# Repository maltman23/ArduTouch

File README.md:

# ArduTouch

ArduTouch is an Arduino-compatible music synthesizer kit.  
Build it, and it works!  
Way low cost (currently $30.)  
It comes with a pre-programmed music synthesizer that makes way cool sounds and music and noise.

An ArduTouch library is available for programming in more super nice synthesizer features, and for making your own synthesizers.
The library comes with examples (with more to come) that serve as a nice tutorial on how to create your own ArduTouch synthesizers (which are Arduino sketches).

ArduTouch is really just an Arduino Uno clone with a small amplifier & speaker, with a PCB touch keyboard, a couple of extra buttons, and a couple of pots (for playing music and controlling the sounds).  The ArduTouch Arduino Library is where the real magic comes from!

For those who want to learn more, the documentation teaches the basics of Digital Signal Processing for audio generation (more documentation coming soon).

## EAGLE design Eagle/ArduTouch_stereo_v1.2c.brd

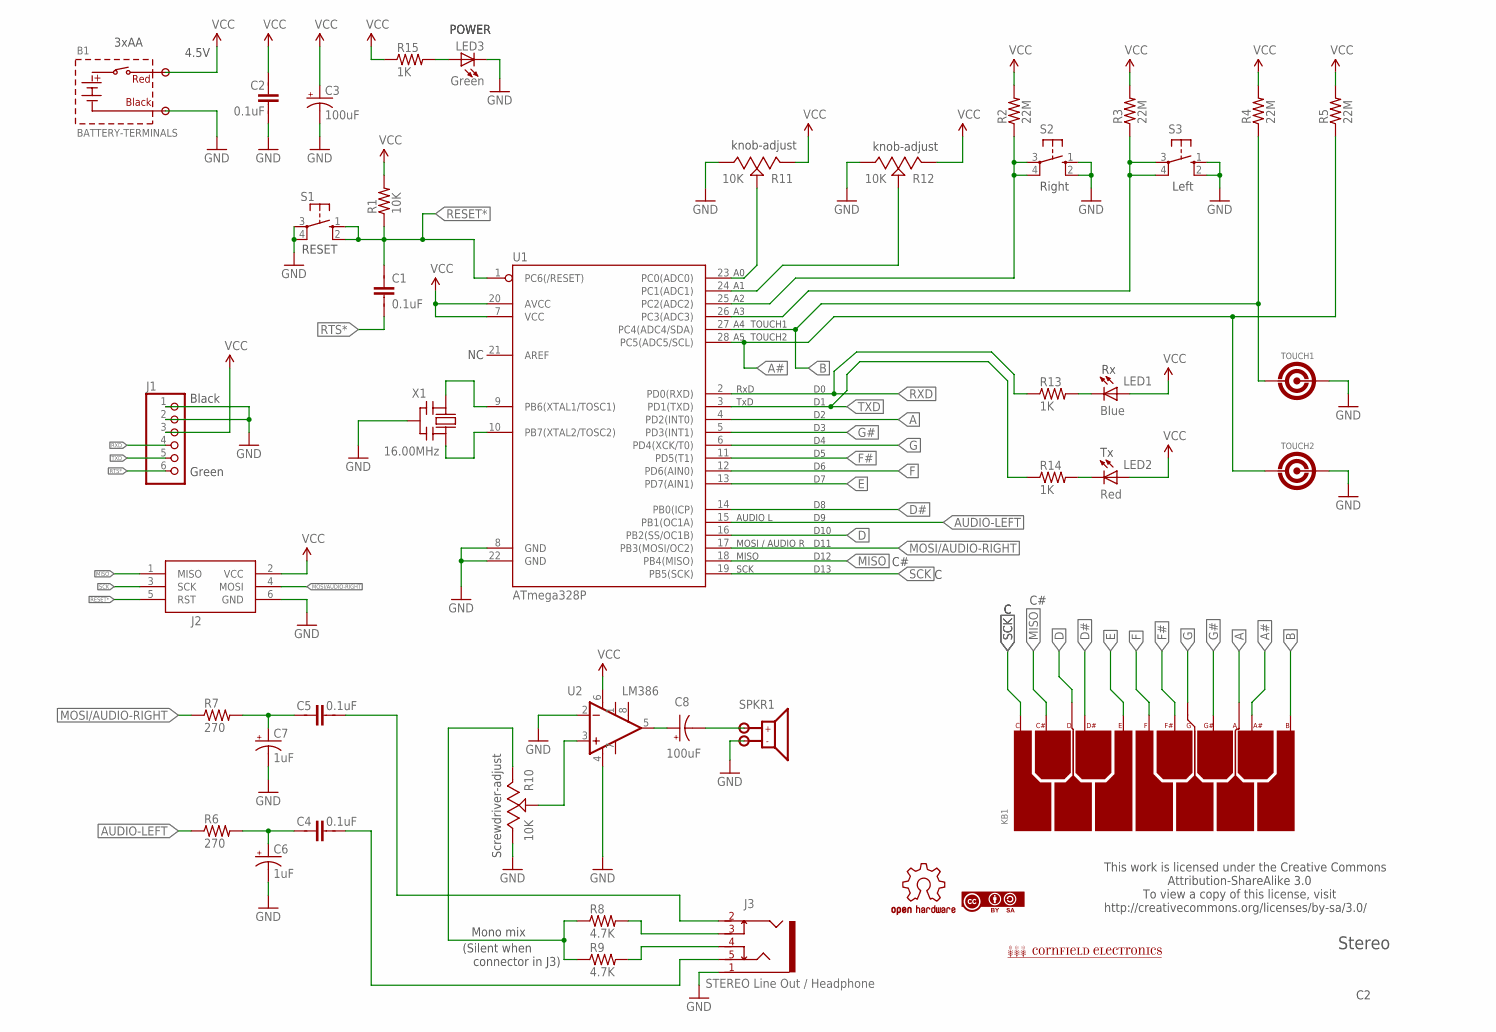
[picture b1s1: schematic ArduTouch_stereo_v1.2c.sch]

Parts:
B1: BATTERY-TERMINALS
C1, C2, C4, C5: 0.1uF; CAP-PTH-SMALL
C3, C8: 100uF; CPOL-RADIAL-10UF-25V
C6, C7: 1uF; CPOL-RADIAL-10UF-25V
J1: PINHD-1X6LOCK; 1X06-BIGLOCK
J2: ISP; AVRISP
J3: STEREO-AUDIO-3.5MM-SWITCHED
KB1: PCB-KEYBOARD4
LED1: Blue; LED5MM
LED2: Red; LED5MM
LED3: Green; LED5MM
R1: 10K; AXIAL-0.4
R2, R3, R4, R5: 22M; AXIAL-0.4
R6, R7: 270; AXIAL-0.4
R8, R9: 4.7K; AXIAL-0.4
R10: 10K; TRIMPOT-3319P-1
R11, R12: 10K; TRIMPOT-72PTR
R13, R14, R15: 1K; AXIAL-0.4
S1, S2, S3: TACTILE_SWITCH_6.3MM
SPKR1: SPEAKER-TERMINALS
TOUCH1, TOUCH2: PCB-TOUCHPAD2
U1: ATmega328P; DIL28-3
U2: LM386; DIP08
U$1: OSH-LOGO
U$2: CC-BY-SA-LOGO2
U$3: CORNFIELD-LOGO
X1: 16.00MHz; CERM_OSC

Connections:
A: KB1.A, U1.4 (PD2(INT0))
A0: R11.2 (S), U1.23 (PC0(ADC0))
A1: R12.2 (S), U1.24 (PC1(ADC1))
A2: R2.P$1 (1), S2.3, S2.4, U1.25 (PC2(ADC2))
A#: KB1.A#, R5.P$1 (1), TOUCH2.1, U1.28 (PC5(ADC5/SCL))
AUDIO-LEFT: R6.P$1 (1), U1.15 (PB1(OC1A))
B: KB1.B, R4.P$1 (1), TOUCH1.1, U1.27 (PC4(ADC4/SDA))
C+: R3.P$1 (1), S3.3, S3.4, U1.26 (PC3(ADC3))
D: KB1.D, U1.16 (PB2(SS/OC1B))
D#: KB1.D#, U1.14 (PB0(ICP))
E: KB1.E, U1.13 (PD7(AIN1))
F: KB1.F, U1.12 (PD6(AIN0))
F#: KB1.F#, U1.11 (PD5(T1))
G: KB1.G, U1.6 (PD4(XCK/T0))
G#: KB1.G#, U1.5 (PD3(INT1))
GND: B1.-, C2.2, C3.-, C6.-, C7.-, J1.1, J1.2, J2.6 (GND), J3.1, LED3.K (C), R10.A, R11.3 (A), R12.3 (A), S1.3, S1.4, S2.1, S2.2, S3.1, S3.2, SPKR1.-, TOUCH1.2, TOUCH2.2, U1.8 (GND), U1.22 (GND), U2.2 (-IN), U2.4 (V-), X1.P$2 (GND)
MISO: J2.1 (MISO), KB1.C#, U1.18 (PB4(MISO))
MOSI/AUDIO-RIGHT: J2.4 (MOSI), R7.P$1 (1), U1.17 (PB3(MOSI/OC2))
unnamed: C8.-, SPKR1.+
unnamed: U1.9 (PB6(XTAL1/TOSC1)), X1.P$1 (IN)
unnamed: U1.10 (PB7(XTAL2/TOSC2)), X1.P$3 (OUT)
unnamed: C5.1, C7.+, R7.P$2 (2)
unnamed: C8.+, U2.5 (OUT)
unnamed: J3.3, R8.P$2 (2)
unnamed: J3.4, R9.P$2 (2)
unnamed: R10.S, U2.3 (+IN)
unnamed: C5.2, J3.2
unnamed: C4.1, C6.+, R6.P$2 (2)
unnamed: LED1.K (C), R13.P$2 (2)
unnamed: LED2.K (C), R14.P$2 (2)
unnamed: C4.2, J3.5
unnamed: LED3.A, R15.P$2 (2)
unnamed: R8.P$1 (1), R9.P$1 (1), R10.E
RESET*: C1.1, J2.5 (RST), R1.P$1 (1), S1.1, S1.2, U1.1 (PC6(/RESET))
RTS*: C1.2, J1.6
RXD: J1.4, R13.P$1 (1), U1.2 (PD0(RXD))
SCK: J2.3 (SCK), KB1.C, U1.19 (PB5(SCK))
TXD: J1.5, R14.P$1 (1), U1.3 (PD1(TXD))
VCC: B1.+, C2.1, C3.+, J1.3, J2.2 (VCC), LED1.A, LED2.A, R1.P$2 (2), R2.P$2 (2), R3.P$2 (2), R4.P$2 (2), R5.P$2 (2), R11.1 (E), R12.1 (E), R15.P$1 (1), U1.7 (VCC), U1.20 (AVCC), U2.6 (V+)

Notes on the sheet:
Stereo
3xAA
Green
Black
AUDIO L
MOSI / AUDIO R
MISO
SCK
RxD
TxD
knob-adjust
Screwdriver-adjust
4.5V
D10
D11
D12
D13
POWER
RESET
TOUCH1
TOUCH2
STEREO Line Out / Headphone
Mono mix
(Silent when connector in J3)
This work is licensed under the Creative Commons Attribution-ShareAlike 3.0 To view a copy of this license, visit http://creativecommons.org/licenses/by-sa/3.0/
Left
Right

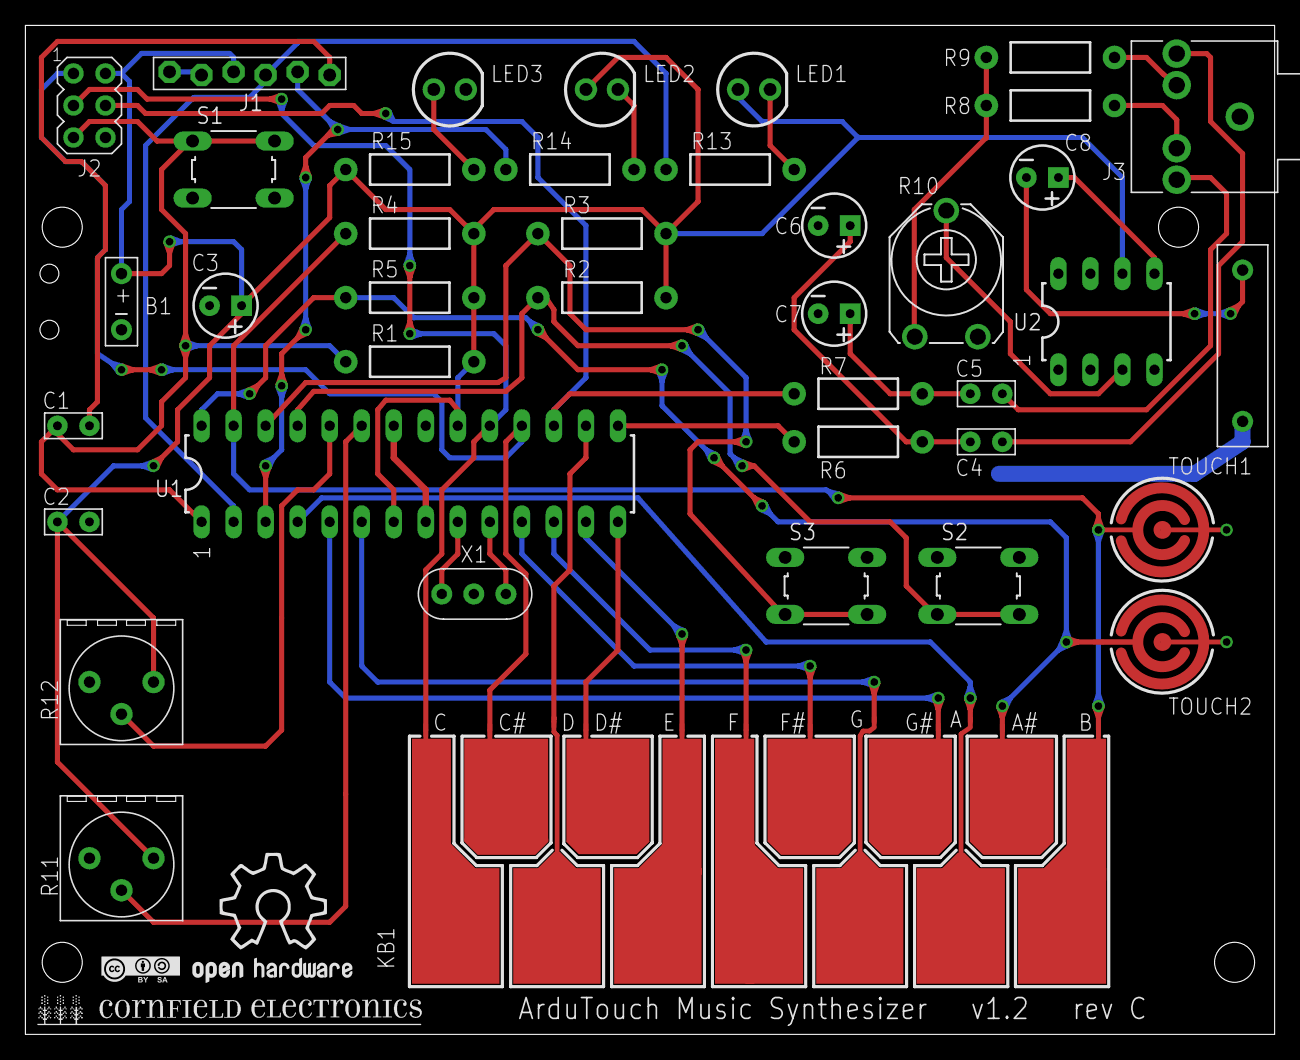
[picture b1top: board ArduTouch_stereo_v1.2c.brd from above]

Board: 2 copper layers, 99.1 x 80.0 mm, 43 parts (0 on the bottom side), 39 nets.

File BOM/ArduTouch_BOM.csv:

Qty,Designator,Part,Mouser/other vendor,mfg,mfg part #
1,B1    ,"3xAA battery holder w/ leads, w/ switch",Jameco: 216144,Jameco,SBH-331-AS-R
4,"C1, C2, C4, C5","0.1uF, 50V, ceramic, 0.1"" spacing leads                   ",594-K104K15X7RF53L2 ,Vishay / BC Components,K104K15X7RF53L2
2,"C3, C8","100uF, 16V or higher, electrolytic, radial, 0.1"" spacing leads",598-107CKS016M ,Cornell Dubilier - CDE,107CKS016M
2,"C6, C7","1uF, 16V or higher, electrolytic, radial, 0.1"" spacing leads",598-105CKR050M,Illinois Capacitor / CDE,105CKR050M
1,J1    ,"1x6, right-angle (FTDI)",649-68016-106HLF,FCI,68016-106HLF
0,J2,not used,,,
1,J3,"headphone, stereo, 3.5mm, switched",806-STX-31205B284C,Kycon,STX-3120-5B-284C
1,LED1  ,"Blue LED, 5mm",941-C5SMFBJFCR0U0351,Cree,C5SMF-BJF-CR0U0351
1,LED2  ,"Red LED, 5mm",941-C5SMFRJFCT0W0BB1,Cree,C5SMF-RJF-CT0W0BB1
1,LED3  ,"Green LED, 5mm",941-C5SMFGJFCV0Y0791,Cree,C5SMF-GJF-CV0Y0791
1,R1,"10K, 1/4W, 5%              ",Jameco: 691104,Jameco,CF1/4W103JRC
4,"R2, R3, R4, R5","22M, 1/4W, 5%",660-CF1/4C226J,KOA Speer,CF1/4C226J
2,"R6, R7","270, 1/4W, 5%",Jameco: 690726,Jameco,CF1/4W271JRC
2,"R8, R9    ","4.7K, 1/4W, 5%",Jameco: 691024,Jameco,CF1/4W472JRC
1,R10,10K trim pot (screwdriver adjust - Volume),652-3319P-1-103,Bourns,3319P-1-103
2,"R11, R12",10K trim pot (knob adjust),858-72PTR10KLF ,BI Technologies / TT Electronics ,72PTR10KLF
3,"R13, R14, R15","1K, 1/4W, 5%",Jameco: 690865,Jameco,CF1/4W102JRC
1,S1,"SPST tact switch, 4-pin, Black button (Reset)",688-SKHHAK,ALPS,SKHHAKA010
2,"S2, S3","SPST tact switch, 4-pin, Red button",688-SKHHAQ,ALPS,SKHHAQA010
1,SPKR1 ,"40mm diameter speaker, 3W, 4 Ohm",665-AS04004PR-R,PUI Audio,AS04004PR-R
1,U1    ,ATmega328P-PU,556-ATMEGA328P-PU,Atmel,ATMEGA328P-PU
1,U2    ,NJM386BD,513-NJM386BD,NJR,NJM386BD
1,X1    ,16.0MHz ceramic resonator,81-CSTLS16M0X55Z-A0,Murata Electronics,CSTLS16M0X55Z-A0
1,PCB,PCB,,,
1,U1 socket,28-pin DIP socket,Jameco: 112299,Jameco,6000-28NDW
0,U2 socket,not used (U2 is soldered directly to PCB),,,
1,small bag,7x10cm reclosable plastic bag,Aliexpress,,
1,large bag,15x22cm reclosable plastic bag,Aliexpress,,
1,label,,,,

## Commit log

2016-04-27 :circus_tent: Added .gitattributes & .gitignore files
2016-04-27 Initial commit
    Initial commit
2016-05-05 ArduTouch assembly instructions
    Initial version of assembly instructions. Mostly just photos, for now.
2016-05-07 ArduTouch schematic
    exported from Eagle
2016-05-07 ArduTouch BOM
    ArduTouch Bill of Materials
2016-12-25 Update to latest PCB, Eagle library parts, Arduino sketches, ArduTouch Arduino Libary, Quick Reference Guide
    V1.2 rev B PCB & Schematic
    ArduTouch Arduino Library v0.63
    DuoPoly V2.23
    Thick V0.38
    Arpology V0.62
    Quick Reference Guide V2.16
2017-11-21 Update to v1.02 of ArduTouch firmware sketches
    ArduTouch Arduino librarie is now very real.
    New example synthesizer sketches in Arduino library.
    Latest versions of synths: DuoPoly, Arpology, and Thick.
    New synth: Beatitude (drum machine).
2017-12-01 in ArduTouch library change default in model.h to __STNDLONE__
    in ArduTouch library change default in model.h to __STNDLONE__
2017-12-16 Update Assembly Instructions, add Programming Guide
    Assembly Instructions now include how to re-program that ArduTouch.
    Added Programming Guide as a separate document.
2018-03-28 Beatitude allows the user to play bass live over the drum sequences, compiles with latest version (V1.8.5) of Arduino IDE
    1) The new version of Beatitude allows the user to play bass live over
    the drum sequences -- i.e. when a drum sequence is being played back by
    the ArduTouch (the red LED is flashing) then the keyboard becomes a bass
    sound that can be played spontaneously over the drum track.
    2) The library now provides "lofi" versions of all the drum samples. The
    example sketch _30_DrumPad.ino contains a discussion of these.
2018-04-07 New Mantra synth; Library has several new base classes
    New Mantra synthesizer, which plays a few layers of Indian-like drone
    music (choice of two drones), with an exotic scale you can play on top
    of it, with an inability to make any music that doesn't sound good. :)
    The library now includes several new base classes, among which are:
    FiltEnv - a dynamic (i.e. enveloped) low-pass filter
    DelayVibrato - adds a delay time before triggering stock vibrato
2018-08-26 updated ArduTouch Arduino library
    new features for effects and sound dynamics, bug fix, new examples for
    tutorials on how to make your own synth sketches
2018-08-27 Added Demo Videos
    Demo Videos for all synthesizers: Arpology (auto-improvise and normal
    play), Beatitude, DuoPoly (4 preset songs), Mantra (drone A and drone
    B), Thick, Xoid.
2018-09-26 Make BOM compatible with Kitspace
2018-09-26 Plot gerbers for v1.2c, include unzipped files
2018-09-26 Add more Mouser part selections/alternatives
2018-09-26 Add kitspace.yaml manifest file
2018-12-22 Make compatible with Kitspace (#6)
    Changes for making the ArduTouch project compatible with Kitspace.org:
    * Make BOM compatible with Kitspace
    * Plot gerbers for v1.2c, include unzipped files
    * Add more Mouser part selections/alternatives
    * Add kitspace.yaml manifest file
2018-12-22 PLEASE USE ARDUINO V1.66 -- New Arduino Library with added features, new ZapShot synth
    ArduTouch Arduino Library v1.09:
    add QuantumOsc module
    add VirtualPot module
    add the virtual method Osc::realFreq()
    Osc::charEv( chrInfo ) displays real, not effective, frequency
    Voice::Voice() sets osc to NULL
2019-02-28 Works with latest Arduino V1.8.8, new sample for drums, added classes, 2 more tutorial examples
    What's New in ArduTouch Release Version 1.10
    --------------------------
    1) The ArduTouch library now works with the latest release of the
    Arduino IDE
    (1.8.8).
    There is a known bug -- recently introduced -- in the Arduino linker,
2019-05-23 New Dronetic synth, added Harmonic Tuning class, added Gain effect
    1) A new synth, Dronetic.ino, is available.
    Dronetic uses 2 drones, each drone is made up of 4 quantum square wave
    oscillators, and the drones are panned dynamically in stereo. You can
    then play a lead over the drones, and the pots control a bunch of
    parameters in real time as you play.
    For an audio demo of Dronetic go to https://www.youtube.com/c/mitchaltman23
2019-10-11 new Quadrant synth, new Envelope classes
    What's New in Version 1.12
    --------------------------
    Works fine with the latest (to date) Arduoino software v1.8.10
    1) A new synth, Quadrant, is released.
    Quadrant features a hybrid stereo effect called an Echotron, which is part
    echo, part arpeggiator, and part pitch shifter.
2019-11-01 fixed some ArduTouch library Examples
    Fixed bugs in some Examples in the ArduTouch library.
2019-12-02 bug fixes in Beatitude and Mantra, updated Quadrant, LFO internals re-written, rearranged tutorial examples in Arduino library, 2 new examples
    What's New in Version 1.13
    --------------------------
    1) LFO internals have been rewritten to use fixed-point 16 bit math instead
    of floating point math, significantly reducing the code footprint.
    There are now four different LFO waveforms available (triangle, square,
    rising sawtooth and falling sawtooth) instead of just one (triangle).
2019-12-27 Fix kitspace.yaml
    That shouldn't have worked the way it was.
2019-12-27 Fix kitspace.yaml (#7)
    That shouldn't have worked the way it was.
2020-01-22 Updated Beatitude, bug fixes in RealTimeSequencer in library, new demo video
    === RELEASE 1.14 ===
    This release is all about Beatitude and the RealTimeSequencer class in the library.
    The new version of Beatitude has these added features:
    1. The drum kit is now panned in stereo.
    2. The top pot controls the balance between the drum kit and the bass.
    3. When recording a sequence with prior versions of Beatitude the 1st
2020-11-01 Update ArduTouchAssembly.pdf
    Update to Assembly Instructions: Better details for section on how to solder
2020-11-01 Definitive version of the library for a standalone ArduTouch card, plus Hocus synth
    This V1.16 release is the definitive version of the library for a standalone ArduTouch card. V1.16 sets the stage for release V1.17, which will (hopefully) implement a MIDI interface via the host.
    What's New in Version 1.16
    -----------------------------------------
    Make sure that the PCB REV of your board (printed near the bottom of the
    ArduTouch card) corresponds to the revision declared in System.h
    0) New Hocus synth
2021-01-03 Create Dronetic_Presets_Demo.mp4
    Added demo video for Dronetic

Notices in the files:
parts and their libraries:
SparkFun-DigitalIC: Licensing: Creative Commons ShareAlike 4.0 International - https://creativecommons.org/licenses/by-sa/4.0
